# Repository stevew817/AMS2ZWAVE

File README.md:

# AMS2ZWAVE
Converter for Norwegian EMI HAN interface to Z-Wave

# Disclaimer
This is a hobby project, and as such will be supported if and when I have the time.

The project is assumed to work for my situation, but it might not work for you. Use at your own risk.

Furthermore, since I am not a member of the Z-Wave SDO, there is no manufacturer/product ID officially assigned to this device.
I don't have the funds required to certify this device, nor the wish to do so myself. This means the IDs in use in this firmware can
be assigned to another manufacturer at any given point in time, breaking the operation of this device in hubs that utilize
device databases (which would be all of them given device configuration parameters are not always discoverable on the network).

Or, more likely, there will be other hobby projects that choose to use the same ID as the default in here.
In that case, you'll have to recompile one of them yourself with a different ID to avoid collisions if they're to be used against the same hub.

If you are affiliated with an SDO-registered company and wish to take this design to market, feel free to do so. I'd appreciate a heads-up, though.

# License
Hardware design is licensed CC-BY: https://creativecommons.org/licenses/by/4.0/

The Z-Wave application code is adapted from a sample application [supplied by Silicon Labs on Github](https://github.com/SiliconLabs/z_wave_applications/tree/1341a074053843d77aac94dc1ba609a796c5856e/z_wave_gesture_sensor_wall_controller_application). The sample applications in that repository are licensed under the Zlib license, and so are my modifications.

Other files that do not originate from the sample application (notably my own HAN parser), are also licensed under the Zlib license.

# Hardware

[PDF Schematic](CAD/AMS2ZWAVE.pdf)

Schematic and board layout are done in KiCAD, and source files can be found in the `CAD` folder.
[Production files for my prototype order](CAD/Gerber/ams2zwave_v1.zip) are also supplied.

## Choice of Z-Wave circuit
I consider this design to be hand-solderable, with the exception of the ZGM130S System-in-Package. Until a Z-Wave 700 series module is
designed and brought to market with a more hobbyist-friendly form factor, you'll have to use a stencil and solder paste to reflow that part.

For prototyping purposes, this design also contains a header to allow it to be wired up to a development kit, instead of having to solder down the ZGM130S.
In that case, the design will act as a bus level translator, power supply and user interface.
For a Silicon Labs WSTK (BRD4001) with ZGM130S plug-in card (BRD4202), wire the `J4` header as follows to the WSTK's `EXP` header:

| Signal | J4  | EXP | ZGM130S |
| ------ | --- | --- | ------- |
| VMCU   | 1   | 2   | (A)VDD(IO) |
| GND    | 5   | 1   | GND |
| HAN_TX | 2   | 6   | PC7 / USART1_RX |
| LED1   | 3   | 13  | PF3 |
| BTN1   | 4   | 9   | PF7 |

## Choice of bus level translation
Norwegian HAN is M-Bus with a twist: all meters observed to date supply 24V 'at rest' (space).
[Mark signal should be 12V under the space voltage](https://m-bus.com/documentation-wired/04-physical-layer), so with that in mind, I have prototyped
two different circuits for converting the HAN signal level to 3V3 TTL.

### Dedicated IC
The 'transceiver' circuit uses an m-bus transceiver, but foregoes using its internal LDO for powering the Z-Wave circuit in favor of a separate DCDC. Avoiding
using the LDO allows the circuit to be much more efficient and not trip any overcurrent protections in the HAN bus master implementation.

Using a transceiver is a more expensive solution, but should also be more reliable in case another meter appears that decides to use actual M-bus voltages (+36/+24)
instead of the currently observed de-facto +24/+12 signal.

Pin-compatible devices are TI's TSS521/TSS721 or ON Semi's NCN5150.

### Opamp
A cheaper alternative (but needs to be validated that it works) is a comparator circuit driven off of the 3V3 supply, looking at the HAN signal through a simple
voltage divider. The resistor values specified would divide the input signal by 12 (i.e. 2V space, 1V mark) and put the reference voltage at 1.75V.

### Setting the jumpers

| Jumper | Function | Default setting (uncut/unsoldered) |
| ------ | -------- | ---------------------------------- |
| JP6 | Connect DCDC output to 3V3 line | connected |
| JP1 | Connect HAN port input 1 to transceiver circuit | unconnected |
| JP2 | Connect HAN port input 2 to transceiver circuit | unconnected |
| JP3 | Connect HAN port input to opamp circuit | unconnected |
| JP5 | Select between normal (1) or inverted (3) transceiver output | normal |
| JP7 | Select between normal (1) or inverted (3) opamp output | normal |
| JP4 | Select source of `HAN_TX` signal between transceiver (1)(output of `JP5`) and opamp (3)(output of `JP7`) circuit  | transceiver / JP5 |

Of note: this circuit won't give you any signal by default. You need to choose to either use the transceiver-based circuit for level translation by soldering
jumpers `JP1` and `JP2`, or select the opamp circuit by soldering `JP3` and moving `JP4` from its default 1-2 position to 2-3.

## DCDC converter and power consumption
The DCDC converter is based around a MAX17531 step-down converter, and designed according to [the datasheet's figure 7](https://datasheets.maximintegrated.com/en/ds/MAX17531.pdf),
*High-Efficiency 3.3V, 50mA Regulator*. Under normal operation, the device will draw about 10 - 14 mA from the 3V3 line, meaning it will be operating at
about 85% efficiency.

This results in a top power draw of about 50mW from the HAN interface (plus the transceiver circuit's static current draw), which is well within spec
for all of the currently deployed meters in Norway. The lowest-power ones (Kamstrup meters) are spec'ed to supply 144mW / 6mA continuously.

## Z-Wave circuit
The circuit was designed based off of the Silicon Labs reference design boards (BRD4202A and BRD8901A, available in Simplicity Studio). Due to the nature
of the SiP, the core design is *extremely* lightweight: 2 decouple caps and an antenna connector. The distance between the SiP and the connector is so short
vs. the wavelength, that impedance control is unlikely to make a difference. The SiP's output is already matched to 50 ohm, so as long as the connected antenna
is also matched to 50 ohms, the design should be good to go.

Debug connector is a 0.05" pitch, 2x5 pinheader. The pinout matches the 'mini simplicity' connector described in Silicon Labs' [application note AN958](https://www.silabs.com/documents/public/application-notes/an958-mcu-stk-wstk-guide.pdf).
This makes it so that the circuit can be debugged by a Silicon Labs development kit [with the appropriate adapter](https://www.silabs.com/development-tools/mcu/32-bit/simplicity-debug-adapter), or
really any other SWD debug probe with the 10-pin ARM connector. Using the Silicon Labs kit gives the possibility to trace energy usage and have a debug serial port
from inside the IDE, though.

The button and activity LED are routed to the same pins as in the Z-Wave SDK's reference applications.

The HAN signal is routed to the Z-Wave SDK's reference application 'USART 1' RX pin. It's a 2400 baud 8-N-1 or 8-E-1 signal.

# Software
The software is an adaptation of the ['Gesture Wall Controller' Z-Wave sample app](https://github.com/SiliconLabs/z_wave_applications/tree/master/z_wave_gesture_sensor_wall_controller_application).

Changes include:
* Stripped out 'central scene' CC and dependencies
* Stripped out associations that are not the lifeline group
* Implemented 'meter' CC
* Changed device type to 'generic meter'
* Bogus manufacturer/product ID
* Implemented a parser for the HAN signal:
    * Uses list identifiers to parse the incoming information. This means a firmware update would be required to support any new meters appearing on the Norwegian market. Shouldn't be much of an issue, since the firmware does support OTA updates.
    * Lives in a [separate repository](http://github.com/stevew817/ams-han-parser)
* Implemented configuration CC to support changing the reporting frequency
    * The Configuration CC should be easily usable by other projects as well, as it was written generically.

Todo:
* Add separate endpoints for getting phase-specific values on three-phase meters (root endpoint currently reports L1 values for voltage and current).
* Add support for reporting both active and reactive power / energy
* Add support for reporting export direction

To build the firmware:
1. Download and install Simplicity Studio
2. Install the Z-Wave SDK inside Simplicity Studio (project was created with Z-Wave SDK 7.15.x)
3. Import this repository (including submodules) as a project into Simplicity Studio
4. Build

To fully flash a blank device:
1. Flash the bootloader (`bin/AMS2ZWAVE-btl-combined.s37`) to the device
    * This is the same bootloader as the SDK-provided one, except it allows firmware downgrading and sidegrading.
2. Flash the sign & encrypt keys to the device, following [step 7 in this guide](https://www.silabs.com/community/wireless/z-wave/knowledge-base.entry.html/2019/04/09/z-wave_700_ota_ofe-i00M)
    * This repository is set up to generate .gbl files using the 'default' keys in the SDK, so you don't have to generate your own
    * For the default keys, flash these files using commander with the --tokenfile argument:
        * `${StudioSdkPath}/protocol/z-wave/BootLoader/sample-keys/sample_encrypt.key`
        * `${StudioSdkPath}/protocol/z-wave/BootLoader/sample-keys/sample_sign.key-tokens.txt`
3. Flash the application like you normally would
4. Verify debug output to check the device is working and responsive

## Z-Wave operation
Device only has a single association group, which is the lifeline group. It will report meter updates unsolicited to the node registered to the lifeline group.
Frequent updates report power draw, whilst the accumulated meter reading is only reported once an hour (see the HAN standard from NEK). This is a limitation of the HAN standard.

The node could theoretically average the reported power draw in-between getting the accumulated meter reading reports, but since some meters only report power for the last second every 10s, that opens up a possibility of averaging higher than actual, and thus 'overestimating' the meter reading within the hour. That would mean the reported accumulated value could potentially go backwards once an hour, and it's not a given that various systems will be able to cope with that.

The controller can ask ('poll') for other values (like voltage and current), but there is currently no support for reporting these automatically.
I consider the use case for grabbing these values fairly narrow, since line voltage shouldn't deviate from 230V too much, and you can calculate backwards from
the reported power draw to get a 'good-enough' estimation of current.

## Development
The root of this repository is importable as a Simplicity Studio project, and targets the Z-Wave SDK version 7.15.4. Both Simplicity Studio and the Z-Wave SDK
are free downloads after registering with Silicon Labs.

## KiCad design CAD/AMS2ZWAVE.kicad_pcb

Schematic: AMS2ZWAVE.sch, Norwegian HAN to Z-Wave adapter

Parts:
C1, C7, C12: 1n; C_0805_2012Metric_Pad1.18x1.45mm_HandSolder
C2, C3, C4, C8, C10, C15: 100n; C_0805_2012Metric_Pad1.18x1.45mm_HandSolder
C5, C6: 1u; C_0805_2012Metric_Pad1.18x1.45mm_HandSolder
C9: 0.22u; C_0805_2012Metric_Pad1.18x1.45mm_HandSolder
C11, C13, C14: 10u; C_0805_2012Metric_Pad1.18x1.45mm_HandSolder
C16: 33u; CP_EIA-2012-12_Kemet-R_Pad1.30x1.05mm_HandSolder
D1: red; LED_PLCC-2
D2: green; LED_PLCC-2
D3, D4: MBR0530; D_SOD-123
D5: NSI50010; D_SOD-123
J1: RJ45_Shielded; RJ45_Amphenol_54602-x08_Horizontal
J2: Conn_Coaxial; U.FL_Molex_MCRF_73412-0110_Vertical
J3: mini simplicity; PinHeader_2x05_P1.27mm_Vertical
J4: Conn_01x05_Male; PinHeader_1x05_P2.54mm_Horizontal
J5: BRD_upper; PinHeader_2x20_P1.27mm_Vertical_SMD
J6: BRD_lower; PinHeader_2x20_P1.27mm_Vertical_SMD
J7: Conn_Coaxial; SMA_Samtec_SMA-J-P-X-ST-EM1_EdgeMount
JP1, JP2: SolderJumper_2_Open; SolderJumper-2_P1.3mm_Bridged_RoundedPad1.0x1.5mm
JP3, JP8: SolderJumper_2_Open; SolderJumper-2_P1.3mm_Open_RoundedPad1.0x1.5mm
JP4, JP5, JP7: SolderJumper_3_Bridged12; SolderJumper-3_P1.3mm_Bridged12_RoundedPad1.0x1.5mm_NumberL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
JP6: SolderJumper_2_Bridged; SolderJumper-2_P1.3mm_Bridged2Bar_RoundedPad1.0x1.5mm
L1: 220uH; L_Taiyo-Yuden_NR-80xx_HandSoldering
R1: 100k; R_0805_2012Metric_Pad1.20x1.40mm_HandSolder
R2: 33k; R_0805_2012Metric_Pad1.20x1.40mm_HandSolder
R3, R10, R11: 3k; R_0805_2012Metric_Pad1.20x1.40mm_HandSolder
R4, R5: 220R; R_0805_2012Metric_Pad1.20x1.40mm_HandSolder
R6: 470R; R_0805_2012Metric_Pad1.20x1.40mm_HandSolder
R7: 82k; R_0805_2012Metric_Pad1.20x1.40mm_HandSolder
R8: 24k; R_0805_2012Metric_Pad1.20x1.40mm_HandSolder
R9: 27k; R_0805_2012Metric_Pad1.20x1.40mm_HandSolder
R12, R18: 1M; R_0805_2012Metric_Pad1.20x1.40mm_HandSolder
R13: 100R; R_0805_2012Metric_Pad1.20x1.40mm_HandSolder
R14: 69.8k; R_0805_2012Metric_Pad1.20x1.40mm_HandSolder
R15: 49.9k; R_0805_2012Metric_Pad1.20x1.40mm_HandSolder
R16: 158k; R_0805_2012Metric_Pad1.20x1.40mm_HandSolder
R17: 22.1R; R_0805_2012Metric_Pad1.20x1.40mm_HandSolder
R19: 130k; R_0805_2012Metric_Pad1.20x1.40mm_HandSolder
SW1: SW_Push; SW_SPST_PTS645
TP1, TP2, TP3, TP4, TP5, TP6, TP7: TestPoint; TestPoint_THTPad_D1.0mm_Drill0.5mm
U1: NCN5150DR2G; On_Semiconductor-NCN5150DR2G
U2: LM358; SOIC-8_3.9x4.9mm_P1.27mm
U3: MAX17531AUB+T; MAX17531AUB&plus_T
U4: ZGM130S

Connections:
+3V3: C4.1, C10.1, C13.1, C14.1, C15.1, J3.1, J4.1, J6.2, JP6.2 (B), R8.2, R11.2, R12.1, U1.9 (VIO), U2.8 (V+), U4.44 (AVDD), U4.52 (VREGVDD), U4.57 (IOVDD)
+VSW: C11.1, JP6.1 (A), L1.2, R16.1, R17.1
HAN+: D3.2 (A), J1.1, JP1.1 (A), JP3.2 (B)
HAN-: C1.2, C2.2, C3.2, C4.2, C5.2, C6.2, C7.2, C8.2, C9.2, C10.2, C11.2, C12.2, C13.2, C14.2, C15.2, C16.2, D1.1 (K), D2.1 (K), J1.2, J1.SH, J2.2 (Ext), J3.2, J4.5, J5.2, J5.38, J6.1, J6.39, J7.2 (Ext), JP2.1 (A), JP8.1 (A), R1.2, R3.1, R6.2, R7.2, R9.1, R13.1, R14.2, R15.2, R19.1, U1.15 (GND), U2.4 (V-), U3.9 (GND), U4.1 (VSS), U4.10 (VSS), U4.11 (VSS), U4.12 (VSS), U4.13 (VSS), U4.14 (VSS), U4.16 (VSS), U4.17 (VSS), U4.18 (VSS), U4.19 (VSS), U4.20 (VSS), U4.21 (VSS), U4.22 (VSS), U4.24 (VSS), U4.25 (VSS), U4.32 (VSS), U4.33 (VSS), U4.40 (PA5), U4.43 (VSS), U4.48 (VSS), U4.49 (VSS), U4.51 (VSS), U4.53 (VSS), U4.54 (VSS), U4.55 (VSS), U4.64 (VSS)
HAN_TX: J4.2, J5.31, J6.6, JP4.2 (C), U4.59 (PC7)
LED_ACT: J4.3, J5.16, R10.2, U4.5 (PF3)
MBUS_PF: U1.5 (PFB)
MBUS_TX: JP4.1 (A), JP5.2 (C)
unnamed: C2.1, R1.1, U1.11 (VDD)
unnamed: C6.1, U1.3 (STC)
unnamed: C8.1, U1.6 (SC)
unnamed: C9.1, R17.2, U3.6 (VOUT)
unnamed: C12.1, R18.1, R19.2, U3.2 (EN/UVLO)
unnamed: C5.1, C16.1, D5.1, R18.2, U3.1 (IN)
unnamed: D1.2 (A), R10.1
unnamed: D2.2 (A), R11.1
unnamed: D3.1 (K), D5.2
unnamed: D4.1 (K), U3.7 (*RESET)
unnamed: J2.1 (In), J7.1 (In), U4.23 (ANTENNA)
unnamed: JP1.2 (B), R4.2
unnamed: JP2.2 (B), R5.2
unnamed: JP3.1 (A), R2.2
unnamed: JP5.1 (A), U1.8 (TX)
unnamed: JP5.3 (B), U1.7 (TXI)
unnamed: JP7.1 (A), U2.1
unnamed: JP7.3 (B), U2.7
unnamed: JP8.2 (B), U3.8 (MODE)
unnamed: L1.1, U3.10 (LX)
unnamed: R4.1, U1.16 (BUSL1)
unnamed: R5.1, U1.1 (BUSL2)
unnamed: R6.1, U1.14 (RIS)
unnamed: R7.1, U1.4 (RIDD)
unnamed: R13.2, SW1.2
unnamed: R14.1, U3.3 (RT/SYNC)
unnamed: R15.1, R16.2, U3.5 (FB)
unnamed: TP1.1, U4.6 (PF4)
unnamed: TP2.1, U4.7 (PF5)
unnamed: TP3.1, U4.8 (PF6)
unnamed: TP4.1, U4.37 (PA2)
unnamed: TP5.1, U4.34 (PD15)
unnamed: TP6.1, U4.60 (PC8)
unnamed: TP7.1, U4.58 (PC6)
OPAMP_TX: JP4.3 (B), JP7.2 (C)
PTI_CLK: U4.41 (PB11)
PTI_DATA: J3.10, J6.23, U4.42 (PB12)
PTI_FRAME: J3.9, J6.25, U4.45 (PB13)
SWCLK: J3.8, J6.27, U4.2 (PF0)
SWDIO: J3.7, J6.29, U4.3 (PF1)
SWO: J3.6, J6.31, U4.4 (PF2)
SW_USR: C7.1, J4.4, J5.26, R12.2, SW1.1, U4.9 (PF7)
VCOM_RX: J3.4, J6.14, U4.36 (PA1)
VCOM_TX: J3.5, J6.12, U4.35 (PA0)
Vdiv: C1.1, R2.1, R3.2, U2.3 (+), U2.6 (-)
Vref: C3.1, R8.1, R9.2, U2.2 (-), U2.5 (+)
nRST: D4.2 (A), J3.3, J5.17, U4.15 (RESETN)

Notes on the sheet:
MBUS Transceiver block
Input connector
Opamp-based receiver block (testing whether this works, much less expensive vs full transceiver)
HAN divided by 12 24V (nominal) -> 2V 14-18V (mark) -> 1.5V
Ref 1.75V
DC/DC converter 12-24V -> 3V3 Reference circuit figure 7 from DS Added Schottky to avoid backpowering DCDC from debug connector
Debug connector
Test and development connector (use only the HAN conversion logic, and wire it to the devkit)
Configurable assignment of input signal. Select between M-Bus transceiver or opamp logic. Default = transceiver.
User interface
Z-Wave System-in-Package Schematic matches BRD4202 / BRD8029
USART1_RX
USART1_TX
USART0_RX
USART0_TX
BRD4202A interface

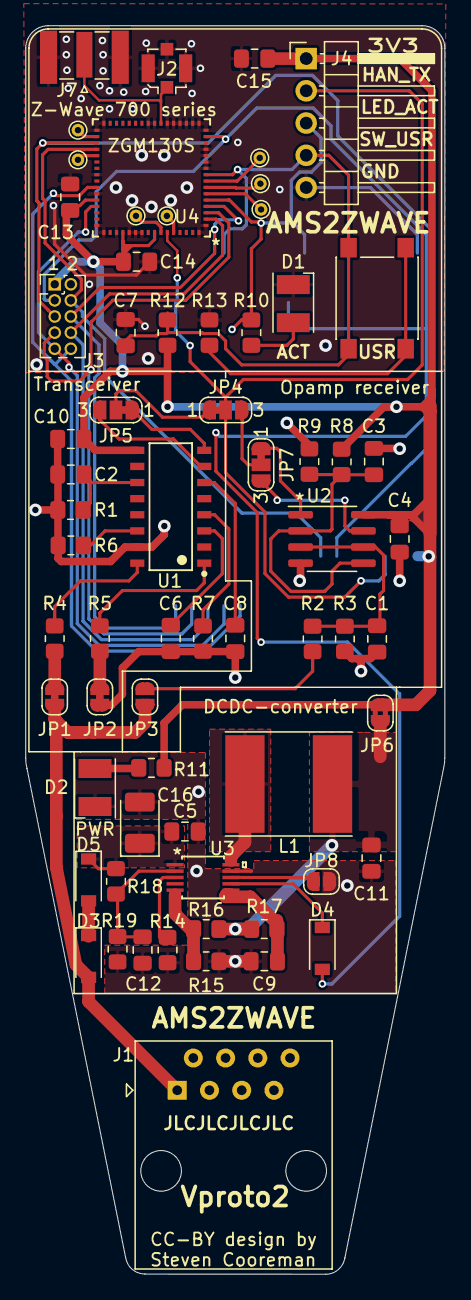
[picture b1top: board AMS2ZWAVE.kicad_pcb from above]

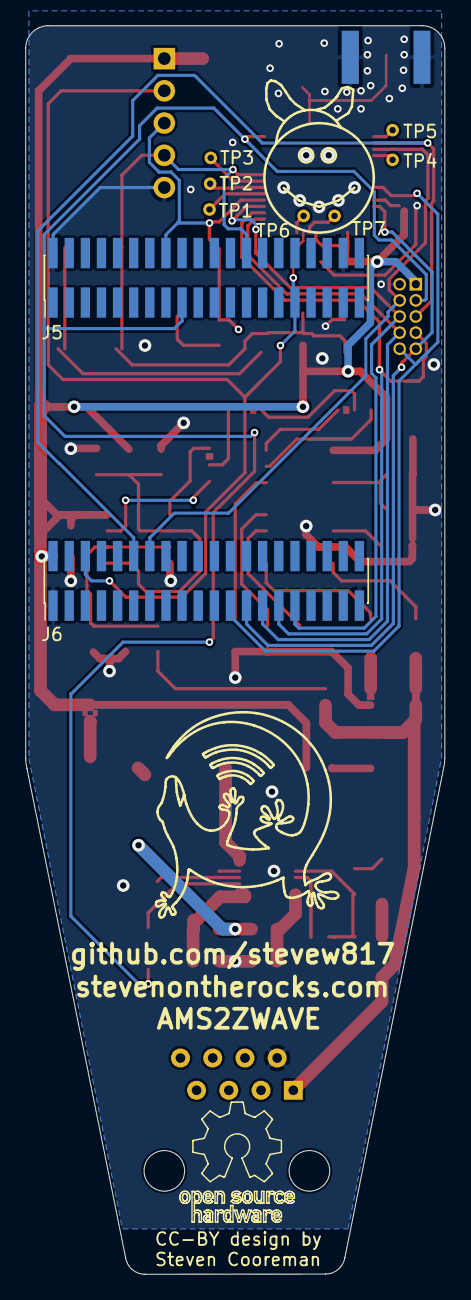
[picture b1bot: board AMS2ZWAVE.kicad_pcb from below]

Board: 2 copper layers, 33.0 x 98.4 mm, 68 parts (2 on the bottom side), 53 nets.

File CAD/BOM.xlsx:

|  |  |  |  |  | prototype build |  | transceiver build |  | opamp build
category | Description | symbol | footprint | part number | unit price | count | total price | count | total price | count | total price | proto stock | Mouser bom
mechanical | SubGHz antenna |  |  | ANTX150P116B08683 | 1.5 | 1 | 1.5 | 1 | 1.5 | 1 | 1.5 |  | X
 | PCB |  |  |  | 1 | 1 | 1 | 1 | 1 | 1 | 1
 | RJ45 connector | J1 | amphenol 54602-x08 | 54602-908LF | 0.5 | 1 | 0.5 | 1 | 0.5 | 1 | 0.5 |  | X
DCDC | DCDC converter | U3 | 10-MSOP | MAX17531AUB | 1.5 | 1 | 1.5 | 1 | 1.5 | 1 | 1.5 |  | X
 | Low-Vf schottky diode, 30V | D3 | SOD-123 | BAT54GWX | 0.1 | 1 | 0.1 | 1 | 0.1 | 1 | 0.1 |  | X
 | Input capacitor, 30V 1uF | C5 | 0805 | CL21B105KBFNNNE | 0.05 | 1 | 0.05 | 1 | 0.05 | 1 | 0.05 |  | X
 | Output capacitor, 5V 10uF low ESR | C11 | 0805 | CL21A106KQFNNNG | 7.0000000000000007E-2 | 1 | 7.0000000000000007E-2 | 1 | 7.0000000000000007E-2 | 1 | 7.0000000000000007E-2 | X | X
 | reference stabilisation cap, 5V 220nF | C9 | 0805 | CL21B224KBFNNNG | 0.05 | 1 | 0.05 | 1 | 0.05 | 1 | 0.05 |  | X
 | Precision resistor 49.9k | R15 | 0805 | RC0805FR-0749K9L | 0.02 | 1 | 0.02 | 1 | 0.02 | 1 | 0.02 |  | X
 | Precision resistor 158k | R16 | 0805 | RC0805FR-07158KL | 0.02 | 1 | 0.02 | 1 | 0.02 | 1 | 0.02 |  | X
 | Precision resistor 140k | R14 | 0805 | RC0805FR-07140KL | 0.02 | 1 | 0.02 | 1 | 0.02 | 1 | 0.02 |  | X
 | Precision resistor 22.1 Ohm | R17 | 0805 | RC0805FR-0722R1L | 0.02 | 1 | 0.02 | 1 | 0.02 | 1 | 0.02 |  | X
 | Low-impedance inductor 220uH | L1 | 8040 | TYS8040221M-10 | 0.3 | 1 | 0.3 | 1 | 0.3 | 1 | 0.3 |  | X
 | Low-Vf schottky diode, 5V | D4 | SOD-123 | BAT54GWX | 0.1 | 1 | 0.1 | 1 | 0.1 | 1 | 0.1 |  | X
Transceiver | mbus transceiver | U1 | SOIC-16 | NCN5150DR2G | 2 | 1 | 2 | 1 | 2 |  |  |  | X
 | Bus termination resistor, 220 Ohm | R4, R5 | 0805 | RC0805FR-0722RL | 0.02 | 2 | 0.04 | 2 | 0.04 |  |  |  | X
 | Bus current set resistor, 470Ohm | R6 | 0805 | RC0805FR-07470RL | 0.02 | 1 | 0.02 | 1 | 0.02 |  |  |  | X
 | Slave current resistor, 82k | R7 | 0805 | RC0805FR-0782KL | 0.02 | 1 | 0.02 | 1 | 0.02 |  |  |  | X
 | transceiver decouple resistor, 100k | R1 | 0805 | RC0805FR-07100KL | 0.02 | 1 | 0.02 | 1 | 0.02 |  |  | X | X
 | Transceiver decouple cap, 100n | C2 | 0805 | CL21B104KCFNNNE | 0.02 | 1 | 0.02 | 1 | 0.02 |  |  | X | X
 | IO decouple cap, 100n | C10 | 0805 | CL21B104KCFNNNE | 0.02 | 1 | 0.02 | 1 | 0.02 |  |  | X | X
 | Bus level storage cap, 100n | C8 | 0805 | CL21B104KCFNNNE | 0.02 | 1 | 0.02 | 1 | 0.02 |  |  | X | X
 | Supply backup cap, 1u | C6 | 0805 | CL21B105KOFNNNG | 0.05 | 1 | 0.05 | 1 | 0.05 |  |  | X | X
Opamp | opamp | U2 | SOIC-8 | LM358LVIDR | 0.3 | 1 | 0.3 |  |  | 1 | 0.3 |  | X
 | decouple cap 100n | C4 | 0805 | CL21B104KCFNNNE | 0.02 | 1 | 0.02 |  |  | 1 | 0.02 | X | X
 | Voltage divider resistor 33k (11/12) | R2 | 0805 | RC0805FR-0733KL | 0.02 | 1 | 0.02 |  |  | 1 | 0.02 |  | X
 | Voltage divider resistor 3k (1/12) | R3 | 0805 | RC0805FR-073KL | 0.02 | 1 | 0.02 |  |  | 1 | 0.02 |  | X
 | Voltage divider resistor 24k (47%) | R8 | 0805 | RC0805FR-0724KL | 0.02 | 1 | 0.02 |  |  | 1 | 0.02 |  | X
 | Voltage divider resistor 27k (53%) | R9 | 0805 | RC0805FR-0727KL | 0.02 | 1 | 0.02 |  |  | 1 | 0.02 |  | X
 | Divider stabilising caps 100n | C1, C3 | 0805 | CL21B104KCFNNNE | 0.02 | 2 | 0.04 |  |  | 2 | 0.04 | X | X
Z-Wave | ZGM130S | U4 | LGA64 | ZGM130S037HGN2R | 6 | 1 | 6 | 1 | 6 | 1 | 6 |  | X
 | ZGM decoupling caps 10uF | C13, C14 | 0805 | CL21A106KQFNNNG | 7.0000000000000007E-2 | 2 | 0.14000000000000001 | 2 | 0.14000000000000001 | 2 | 0.14000000000000001 | X | X
 | U.fl / ipex connector | J2 | U.fl | Molex 73412-0110 | 0.6 | 1 | 0.6 | 1 | 0.6 | 1 | 0.6 |  | X
 | Mini simplicity connector | J3 | .05" 2x5 male header | 20021111-00010T1LF | 0.5 | 1 | 0.5 | 0 | 0 | 0 | 0 |  | X
 | Prototype connector | J4 | right-angle .1" pinhd | 10129379-905001BLF | 0.08 | 1 | 0.08 | 0 | 0 | 0 | 0 | X | X
 | Input decouple prototype 100n | C15 | 0805 | CL21B104KCFNNNE | 0.02 | 1 | 0.02 | 0 | 0 | 0 | 0 | X | X
 | LED current limiting resistors 3k | R10, R11 | 0805 | RC0805FR-073KL | 0.02 | 2 | 0.04 | 2 | 0.04 | 2 | 0.04 |  | X
 | Power-on indicator LED, red | D1 | PLCC2 | CLM3C-RKW-CUBVAAA3 | 0.15 | 1 | 0.15 | 1 | 0.15 | 1 | 0.15 |  | X
 | Zwave activity LED, amber | D2 | PLCC2 | CLM3C-AKW-CUAVB253 | 0.15 | 1 | 0.15 | 1 | 0.15 | 1 | 0.15 |  | X
 | Zwave user button | SW1 | 6x6mm | PTS645SK50SMTR92LFS | 0.14000000000000001 | 1 | 0.14000000000000001 | 1 | 0.14000000000000001 | 1 | 0.14000000000000001 |  | X
 | User button pullup 1M | R12 | 0805 | RC0805FR-071ML | 0.04 | 1 | 0.04 | 1 | 0.04 | 1 | 0.04 |  | X
 | User button snubber cap 1n | C7 | 0805 | CL21B102KBANNNC | 0.04 | 1 | 0.04 | 1 | 0.04 | 1 | 0.04 |  | X
 | User button snubber r, 100 Ohm | R13 | 0805 | RC0805FR-07100RL | 0.02 | 1 | 0.02 | 1 | 0.02 | 1 | 0.02 | X | X
 |  |  |  |  | USD |  | 15.81999999999999 |  | 14.779999999999992 |  | 13.009999999999993

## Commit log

2020-12-29 Initial WIP
2020-12-29 Add schematic and PCB for prototype version
2020-12-29 Added BOM
2020-12-29 Add schematic in PDF
2020-12-29 Avoid deletion of file links on cleaning git repo
2020-12-29 Update HAN parser
    * Add license headers
    * Add entries for Kamstrup and Kaifa meters
    * Update DB struct format
2020-12-29 Update typedefs with namespacing
2020-12-29 Pull out platform dependencies from HAN parser logic
2020-12-29 Update HAN parser to be standalone
2020-12-29 Move readings out of HAN parser
2020-12-29 Checked HAN parser against known data and fixed some bugs
2020-12-29 Slightly better doc for hanparser platform implementation
2020-12-29 HAN parser is ready for prime-time
2020-12-29 HAN parser semantic cleanup
2020-12-29 Remove AMS-HAN parser from index
2020-12-29 Add back AMS HAN parser as submodule
2020-12-29 Submodule sync
2020-12-29 Initial README
2020-12-29 Doc update
2020-12-29 Track last reported power
2020-12-29 Implement USART Rx in a better way
    Using task notification instead of event, and changing the buffer format, stopped the application from crashing.
2020-12-29 Fully move to RX on task notify instead of event queue
2020-12-29 Move app data reset to own function
2020-12-29 First implementation of Configuration CC
    Sweet jesus, this is a lot of boilerplate that could've been part of the SDK...
2020-12-29 Fix configuration CC info/name
    By moving consecutive packet sending into a callback function, we prevent
    exhausting the node's send queue.
2020-12-29 Added support for polling voltage and current on L1
    three-phase will have to wait for multi-endpoint support
2020-12-29 Store reset point to memory as it happens
2020-12-29 Pull up Configuration CC handling into its own file
    I think the Configuration CC is now ready to rock & roll as a generic configuration component...
2020-12-29 Turn on HAN RX on USART1 @ 2400 baud
2020-12-29 Minor updates
    * Added custom bootloader to the project for supporting OTA
    * Print DSK at boot for SmartStart
    * doc patch
2020-12-29 Add bootloader instructions
2020-12-29 Fixed a bug causing smartstart to not work
2020-12-30 set option to enumerated
2020-12-30 Spec says we always have to respond to meter get requests
    This might be sucky from a user experience, if values haven't refreshed yet.
2020-12-31 Configuration CC: use 16-bit parameter numbers
2020-12-31 Clarify CC_Configuration
2020-12-31 Configuration CC: added bulk commands handling
2020-12-31 actually save updated parameters
2021-01-10 PCB iteration 2
    * Added inrush current limiter
    * Added footprint to use BRD4202 instead of soldering down ZGM130S
2021-01-10 Debugprint tweaks
2021-01-11 Fix Configuration CC for Bulk Report
    After feedback from N2641D
2021-01-11 Use sizeof_array convenience macro
2021-01-12 Apply feedback by @N2641D
2021-01-15 Update to v2 PCB
    * Increased DCDC switching frequency to 600kHz
    * Added resistor divider for setting UVLO to 10V
    * Added solderjumper for DCDC mode
    * Added bulk capacitor to smooth out 12V swings on the input line
2021-01-16 Update to proto v2
    * Added edgemount SMA in addition to U.FL for antenna flexibility
2021-01-16 Update to proto v2
    * Added test points for LGA pads bordering on in-use pads, to avoid them from coming loose when too much heat is applied
    * Moved SMA edge connector around, it makes more sense to have it at the top
    * Tidied layout
2021-01-17 Added missing 3D models for SMA and RJ45 connectors
2021-01-26 It's minus 10 degrees outside and I don't want to freeze
    Postponing debugging to a warmer season. This workaround is good
    enough, and nobody is ever likely to notice.
2021-01-26 It's *still* extremely cold outside and resetting every 2-3h wasn't enough
2021-02-02 Temporarily piggyback off of voltage and current for debugging
    Hopefully I can figure out why it was halting without having to
    stand outside in the cold for hours with a debugger.
2021-02-09 Set UART priorities lower than the radio's
    Could potentially solve the hanging mystery?

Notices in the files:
CAD/AMS2ZWAVE.kicad_pcb:
CC-BY design by
Steven Cooreman
CAD/AMS2ZWAVE.sch:
CC-BY design by Steven Cooreman
parts and their libraries:
Copyright 2016 Accelerated Designs. All rights reserved.
